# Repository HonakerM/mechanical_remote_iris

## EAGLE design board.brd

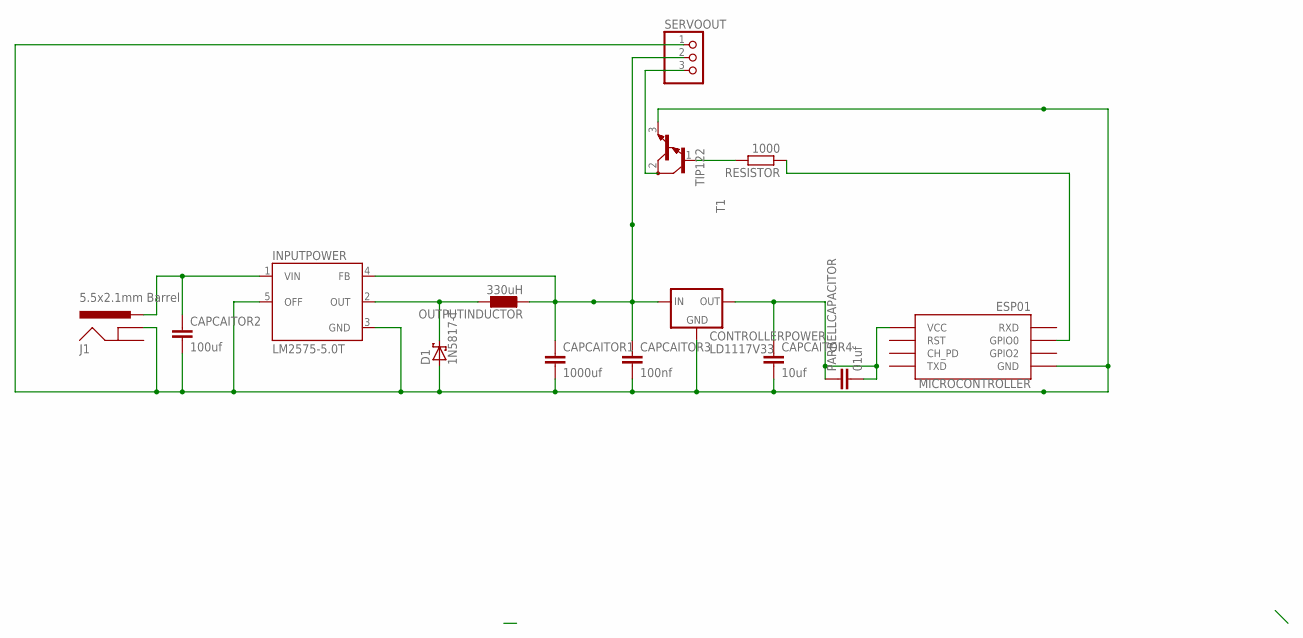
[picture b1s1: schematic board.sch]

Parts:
CAPCAITOR1: 1000uf; C5B2.5
CAPCAITOR2: 100uf; C5B2.5
CAPCAITOR3: 100nf; C5B2.5
CAPCAITOR4: 10uf; C5B2.5
CONTROLLERPOWER: LD1117V33
D1: 1N5817-T; DO41-7.6
INPUTPOWER: LM2575-5.0T; TO220-5
J1: 5.5x2.1mm Barrel; POWER_JACK_SMD
MICROCONTROLLER: ESP01
OUTPUTINDUCTOR: 330uH; 0204/7
PARRELLCAPACITOR: 01uf; C5B2.5
RESISTOR: 1000; 0207/10
SERVOOUT: PINHD-1X3; 1X03
T1: TIP122; TO220

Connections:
GND: CAPCAITOR1.2, CAPCAITOR2.2, CAPCAITOR3.2, CAPCAITOR4.2, CONTROLLERPOWER.GND, D1.A, INPUTPOWER.3 (GND), INPUTPOWER.5 (OFF), J1.GND (GNDBREAK), MICROCONTROLLER.GND, SERVOOUT.1, T1.3 (E)
unnamed: CAPCAITOR2.1, INPUTPOWER.1 (VIN), J1.VIN0 (PWR)
unnamed: D1.C, INPUTPOWER.2 (OUT), OUTPUTINDUCTOR.1
unnamed: CAPCAITOR1.1, CAPCAITOR3.1, CONTROLLERPOWER.IN, INPUTPOWER.4 (FB), OUTPUTINDUCTOR.2, SERVOOUT.2
unnamed: CAPCAITOR4.1, CONTROLLERPOWER.OUT, MICROCONTROLLER.VCC, PARRELLCAPACITOR.1, PARRELLCAPACITOR.2
unnamed: RESISTOR.2, T1.1 (B)
unnamed: MICROCONTROLLER.GPIO0, RESISTOR.1
unnamed: SERVOOUT.3, T1.2 (C)

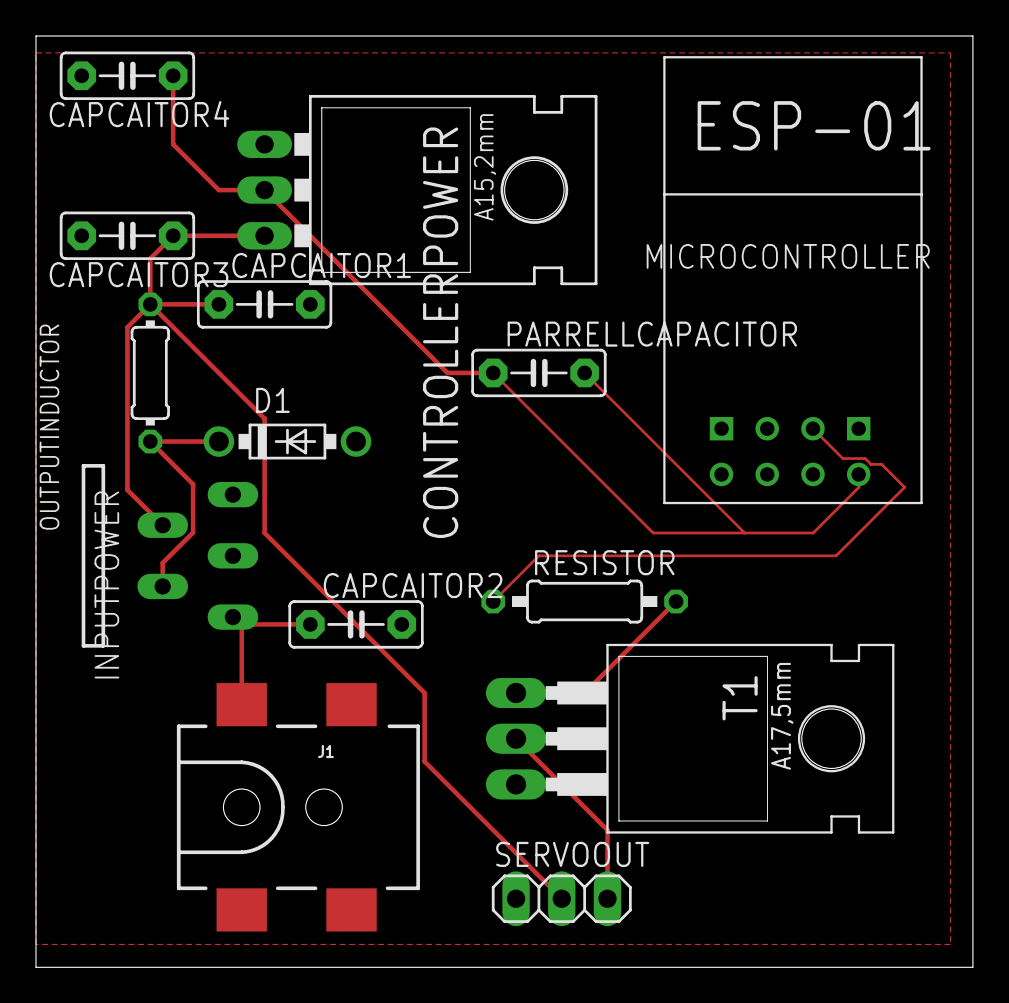
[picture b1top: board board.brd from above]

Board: 2 copper layers, 52.0 x 51.7 mm, 14 parts (0 on the bottom side), 8 nets.

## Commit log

2019-01-01 Update V1 Schematic
2019-01-02 Change Base board to esp-12f
    Simplify and improve performance
2019-01-02 Updated with Gerber files
2019-01-10 Change base board to esp 01
2019-01-10 Added autocad drawings
2019-01-10 Board update and autocad update to add nx files
2019-01-11 Updated PCB and Gerber Files
2019-01-11 Separated nx files
2019-02-27 Updated file structure
2019-03-01 Update Board

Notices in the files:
parts and their libraries:
SparkFun-Connectors: Licensing: Creative Commons ShareAlike 4.0 International - https://creativecommons.org/licenses/by-sa/4.0
